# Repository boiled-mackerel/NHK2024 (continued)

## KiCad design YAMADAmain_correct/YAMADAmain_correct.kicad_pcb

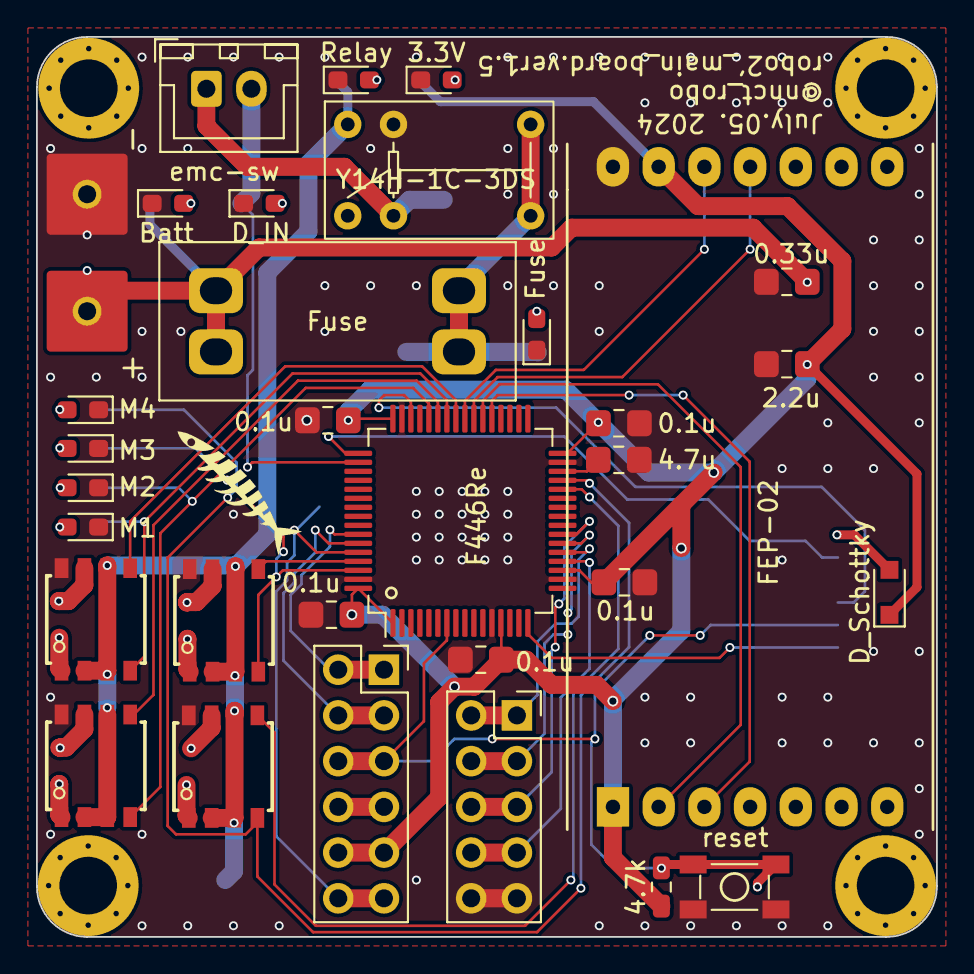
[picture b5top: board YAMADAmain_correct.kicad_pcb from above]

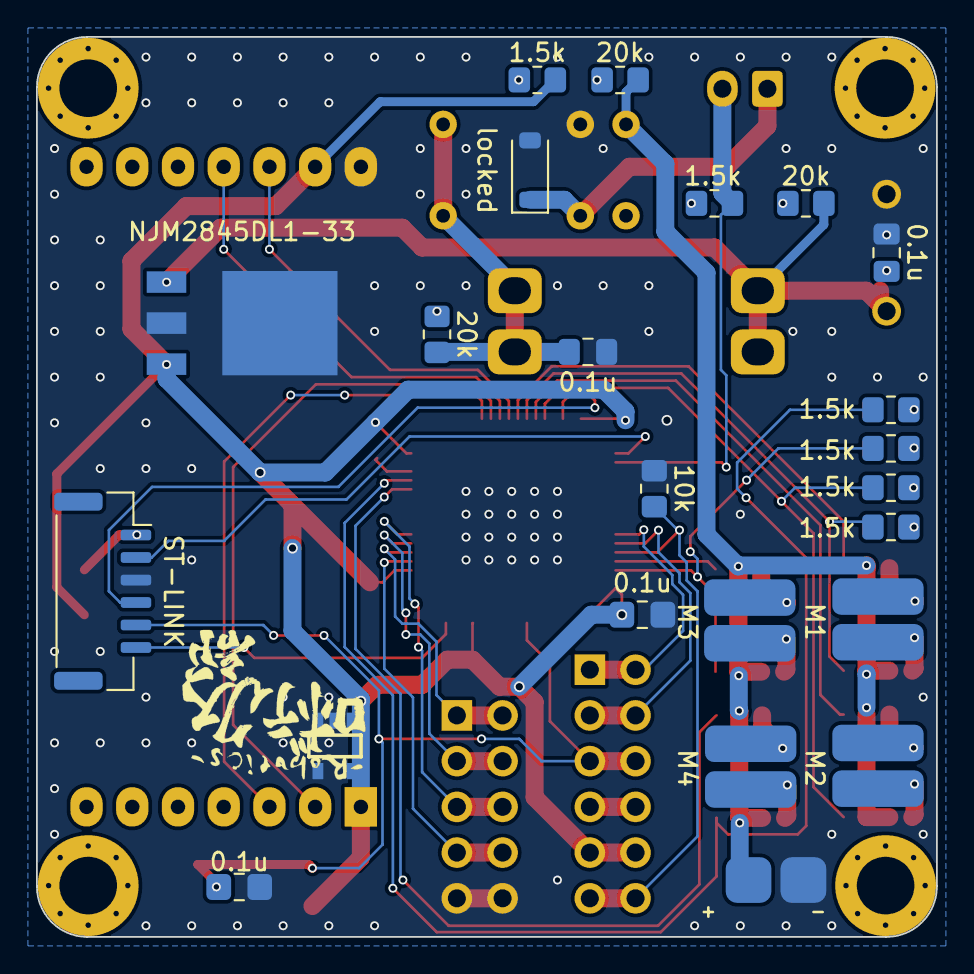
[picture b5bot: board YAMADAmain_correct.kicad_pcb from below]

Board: 2 copper layers, 50.0 x 50.0 mm, 54 parts (22 on the bottom side), 50 nets.

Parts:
B_C1: 0.1u; C_0805_2012Metric_Pad1.18x1.45mm_HandSolder
C1: 0.33u; C_0805_2012
C2: 2.2u; C_0805_2012
D2: 3.3V; LED_0603_1608Metric_Pad1.05x0.95mm_HandSolder
D3: Batt; LED_0603_1608Metric_Pad1.05x0.95mm_HandSolder
D4: Fuse; LED_0603_1608Metric_Pad1.05x0.95mm_HandSolder
D5: D_IN; LED_0603_1608Metric_Pad1.05x0.95mm_HandSolder
D6: locked; D_SOD-123
D7: Relay; LED_0603_1608Metric_Pad1.05x0.95mm_HandSolder
D8: M4; LED_0603_1608Metric_Pad1.05x0.95mm_HandSolder
D9: M3; LED_0603_1608Metric_Pad1.05x0.95mm_HandSolder
D10: M2; LED_0603_1608Metric_Pad1.05x0.95mm_HandSolder
D11: M1; LED_0603_1608Metric_Pad1.05x0.95mm_HandSolder
F1: Fuse; FuseHolder_Carfuse
F_C1: 0.1u; C_0805_2012Metric_Pad1.18x1.45mm_HandSolder
IC1: BD7LS04G-CTL; SOT95P280X125-5N
J1: BATT; POWER_PAD
J2: Conn_02x06_Counter_Clockwise; PinSocket_2x06_P2.54mm_Vertical
J3: emc-sw; JST_XH_B2B-XH-A_1x02_P2.50mm_Vertical
J4: Conn_02x05_Counter_Clockwise; PinSocket_2x05_P2.54mm_Vertical
J5: motor1; min_motor
J6: motor2; min_motor
J7: motor3; min_motor
J8: motor4; min_motor
R1: 10k; R_0805_2012Metric_Pad1.20x1.40mm_HandSolder
R2, R5, R7, R8, R9, R10: 1.5k; R_0805_2012Metric_Pad1.20x1.40mm_HandSolder
R3, R4, R6: 20k; R_0805_2012Metric_Pad1.20x1.40mm_HandSolder
U1: NJM2845DL1-33
U2: FEP-02; FEP-02_PIN_SOCKET
U3: Y14H-1C-3DS
U4, U5, U6, U7: SOP8
U8: 4.7k; R_0603_1608
U9: D_Schottky; smd_diode_SOD-323_HandSoldering_cus10f30
U10: SW_DP3T; tact_sw_smd_skrpabe10
U11, U12, U14, U17, U18, U20, U21: 0.1u; C_0805_2012
U13: ST-LINK; JST_GH_SM06B-GHS-TB_1x06-1MP_P1.25mm_Horizontal
U15: 4.7u; C_0805_2012
U16: STM32F446RETx-stm32; LQFP-64_10x10mm_P0.5mm

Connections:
+3.3V: C2.1, J2.9, J2.10, R2.2, U1.3 (Vout), U2.1 (VCC(2.5v-5.5v)), U2.13 (PowerOn), U8.1, U9.1 (K), U12.1, U14.1, U16.1 (VBAT), U16.13 (VDDA), U16.19 (VDD), U16.32 (VDD), U16.48 (VDD), U16.64 (VDD), U17.1, U18.1, U20.1, U21.1
+5V: J2.7, J2.8
BAT: B_C1.1, C1.1, F1.1, J1.1, R3.2, U1.1 (Vin)
BOOT0: J2.11, J2.12, R1.1, U16.60 (BOOT0)
EMC_IN: J3.2, R5.2, U16.50 (ADC1_EXTI15/ADC2_EXTI15/ADC3_EXTI15/CEC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)
FEP_INI: U2.11 (/INI), U16.39 (PC8/DCMI_D2/SDIO_D0/SYS_TRACED0/TIM3_CH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)
FEP_RST: U2.12 (/RST), U16.40 (PC9/DAC_EXTI9/DCMI_D3/I2C3_SDA/I2S_CKIN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)
Fuse_out: F1.2, F_C1.1, R4.1, U3.3, U3.6
GND: B_C1.2, C1.2, C2.2, D2.1 (K), D3.1 (K), D4.1 (K), D5.1 (K), D6.2 (A), D7.1 (K), D8.1 (K), D9.1 (K), D10.1 (K), D11.1 (K), F_C1.2, J1.2, J4.9, J4.10, R1.2, U1.2 (GND), U2.14 (GND), U3.5, U4.8 (GND), U5.8 (GND), U6.8 (GND), U7.8 (GND), U10.2, U10.4, U11.1, U12.2, U13.3, U14.2, U15.2, U16.12 (VSSA), U16.18 (VSS), U16.31 (VSS), U16.47 (VSS), U16.63 (VSS), U17.2, U18.2, U20.2, U21.2
M1FIN: R10.2, U4.4 (FIN), U16.42 (DAC_EXTI9/DCMI_D0/I2C3_SMBA/I2S2_CK/SAI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)
M1RIN: U4.5 (RIN), U16.41 (I2C3_SCL/RCC_MCO_1/TIM1_CH1/USART1_CK/U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)
M2FIN: R9.2, U5.4 (FIN), U16.44 (ADC1_EXTI11/ADC2_EXTI11/ADC3_EXTI11/CAN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)
M2RIN: U5.5 (RIN), U16.43 (DCMI_D1/TIM1_CH3/USART1_RX/USB_OTG_FS_I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)
M3FIN: R8.2, U6.4 (FIN), U16.62 (CAN1_TX/DAC_EXTI9/DCMI_D7/I2C1_SDA/I2S2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)
M3RIN: U6.5 (RIN), U16.61 (CAN1_RX/DCMI_D6/I2C1_SCL/SDIO_D4/TIM10_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)
M4FIN: R7.2, U7.4 (FIN), U16.29 (I2C2_SCL/I2S2_CK/SAI1_SCK_A/SPI2_SCK/TI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)
M4RIN: U7.5 (RIN), U16.28 (BOOT1/I2S3_SD/QUADSPI_CLK/SAI1_SD_A/SDI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)
MISO: J4.3, J4.4, U16.22 (ADC1_IN6/ADC2_IN6/DCMI_PIXCLK/I2S2_MCK/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)
MOSI: J4.5, J4.6, U16.23 (ADC1_IN7/ADC2_IN7/I2S1_SD/SPI1_MOSI/TIM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)
NSS: J4.7, J4.8, U16.20 (ADC1_IN4/ADC2_IN4/DAC_OUT1/DCMI_HSYNC/I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)
unnamed: D2.2 (A), R2.1
unnamed: D3.2 (A), R3.1
unnamed: D4.2 (A), R4.2
unnamed: D5.2 (A), R5.1
unnamed: D6.1 (K), J3.1, U3.2
unnamed: D7.2 (A), R6.1
unnamed: D8.2 (A), R7.1
unnamed: D9.2 (A), R8.1
unnamed: D10.2 (A), R9.1
unnamed: D11.2 (A), R10.1
unnamed: U9.2 (A), U13.1
unnamed: U15.1, U16.30 (VCAP_1)
PC_6_Serial6TX: U2.3 (TXD(DataIn)), U16.37 (PC6/DCMI_D0/FMPI2C1_SCL/I2S2_MCK/SDIO_D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)
PC_7_Serial6RX: U2.2 (RXD(DateOut)), U16.38 (PC7/DCMI_D1/FMPI2C1_SDA/I2S2_CK/I2S3_MC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)
RESET: J2.5, J2.6, U8.2, U10.1, U10.3, U11.2, U13.5, U16.7 (NRST)
Relay_out: R6.2, U3.4, U4.2 (VCC), U4.3 (VCC), U4.6 (VREF), U5.2 (VCC), U5.3 (VCC), U5.6 (VREF), U6.2 (VCC), U6.3 (VCC), U6.6 (VREF), U7.2 (VCC), U7.3 (VCC), U7.6 (VREF)
SCK: J4.1, J4.2, U16.21 (ADC1_IN5/ADC2_IN5/DAC_OUT2/I2S1_CK/SPI1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)
ST-LINK(TX): U13.6, U16.16 (ADC1_IN2/ADC2_IN2/ADC3_IN2/TIM2_CH3/TIM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)
SWCLK: U13.2, U16.49 (SYS_JTCK-SWCLK/PA14)
SWDIO: U13.4, U16.46 (SYS_JTMS-SWDIO/PA13)
U0RXD: J2.1, J2.2, U16.58 (CAN2_TX/CEC/DCMI_D5/I2C1_SCL/QUADSPI_BK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)
U0TXD: J2.3, J2.4, U16.59 (DCMI_VSYNC/I2C1_SDA/SPDIFRX_IN0/TIM4_CH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)
motor1_A: J5.1, U4.1 (OUT1)
motor1_B: J5.2, U4.7 (OUT2)
motor2_A: J6.1, U5.1 (OUT1)
motor2_B: J6.2, U5.7 (OUT2)
motor3_A: J7.1, U6.1 (OUT1)
motor3_B: J7.2, U6.7 (OUT2)
motor4_A: J8.1, U7.1 (OUT1)
motor4_B: J8.2, U7.7 (OUT2)

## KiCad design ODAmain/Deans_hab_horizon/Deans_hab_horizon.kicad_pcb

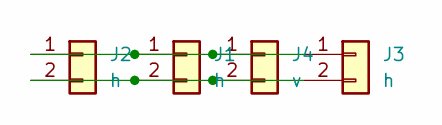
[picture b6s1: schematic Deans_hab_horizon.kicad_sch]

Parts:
J1, J2, J3: h; deans_horizontal
J4: v; Deans_Female

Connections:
unnamed: J1.1, J2.1, J3.1, J4.1
unnamed: J1.2, J2.2, J3.2, J4.2

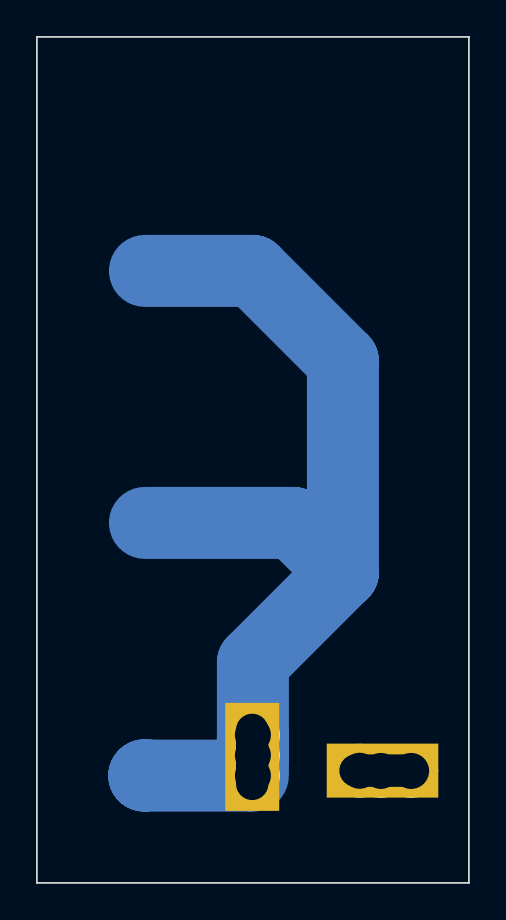
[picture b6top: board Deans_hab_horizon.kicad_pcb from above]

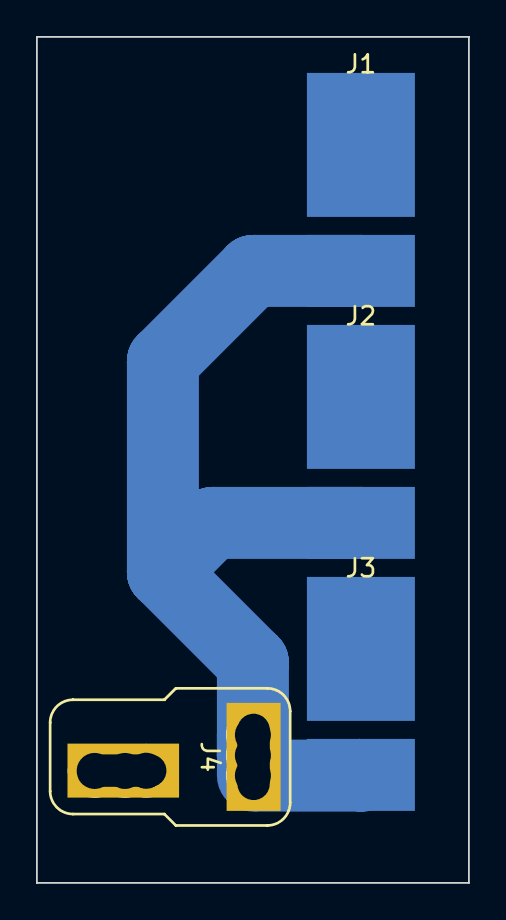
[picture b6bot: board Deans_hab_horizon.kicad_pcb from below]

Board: 2 copper layers, 24.0 x 47.0 mm, 4 parts (4 on the bottom side), 2 nets.

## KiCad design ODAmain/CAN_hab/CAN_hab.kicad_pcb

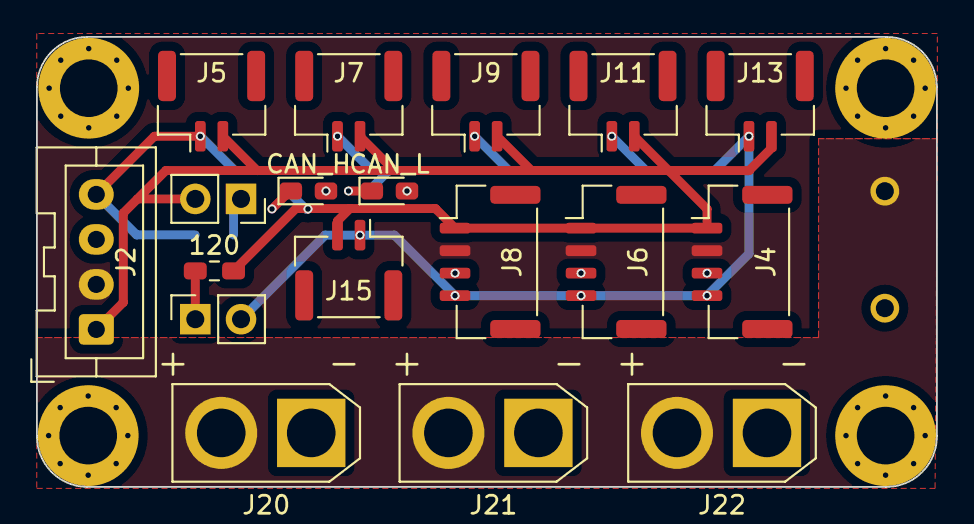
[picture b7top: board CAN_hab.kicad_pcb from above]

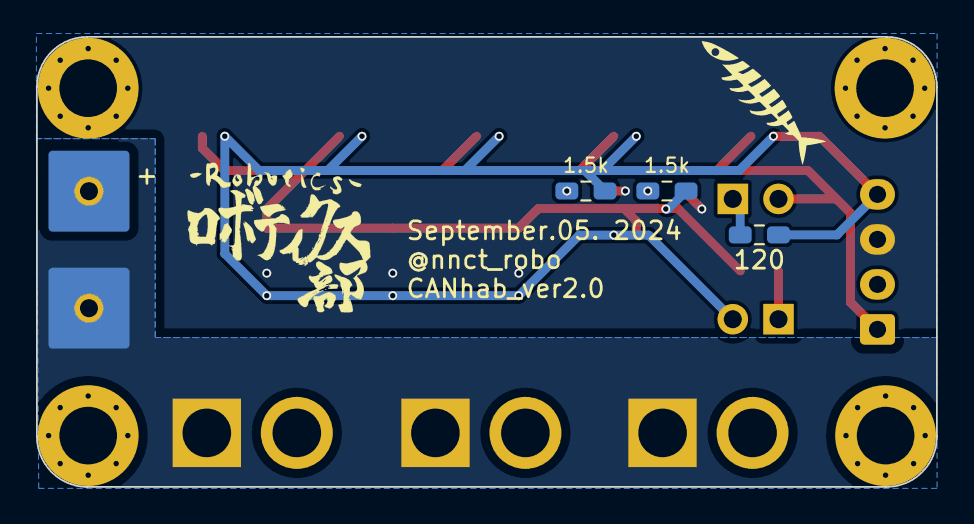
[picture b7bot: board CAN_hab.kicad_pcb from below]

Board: 2 copper layers, 50.0 x 25.0 mm, 22 parts (4 on the bottom side), 10 nets.

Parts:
+: XT30; POWER_PAD_normal
D1: CAN_H; LED_0603_1608
D2: CAN_L; LED_0603_1608
J1, J19: Terminate; PinSocket_1x02_P2.54mm_Vertical
J2: xh; JST_XA_B04B-XASK-1_1x04_P2.50mm_Vertical
J4: gh*4_1; JST_GH_BM04B-GHS-TBT_1x04-1MP_P1.25mm_Vertical
J5: gh*2_1; JST_GH_BM02B-GHS-TBT_1x02-1MP_P1.25mm_Vertical
J6: gh*4_2; JST_GH_BM04B-GHS-TBT_1x04-1MP_P1.25mm_Vertical
J7: gh*2_2; JST_GH_BM02B-GHS-TBT_1x02-1MP_P1.25mm_Vertical
J8: gh*4_3; JST_GH_BM04B-GHS-TBT_1x04-1MP_P1.25mm_Vertical
J9: gh*2_3; JST_GH_BM02B-GHS-TBT_1x02-1MP_P1.25mm_Vertical
J11: gh*2_4; JST_GH_BM02B-GHS-TBT_1x02-1MP_P1.25mm_Vertical
J13: gh*2_5; JST_GH_BM02B-GHS-TBT_1x02-1MP_P1.25mm_Vertical
J15: gh*2_6; JST_GH_BM02B-GHS-TBT_1x02-1MP_P1.25mm_Vertical
J20, J21, J22: XT30; AMASS_XT30U-F_1x02_P5.0mm_Vertical
R1, R4: 120; R_0603_1608
R2, R3: 1.5k; R_0603_1608

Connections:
+5V: J2.2, J4.2, J6.2, J8.2
+BATT: +.2, J20.2, J21.2, J22.2
CAN_H: J2.1, J4.1, J5.2, J6.1, J7.2, J8.1, J9.2, J11.2, J13.2, J15.2, J19.2, R1.1, R2.1
CAN_L: J1.2, J2.4, J4.4, J5.1, J6.4, J7.1, J8.4, J9.1, J11.1, J13.1, J15.1, R3.1, R4.1
GND: D1.1 (K), D2.1 (K), J2.3, J4.3, J6.3, J8.3
GNDPWR: +.1, J20.1, J21.1, J22.1
unnamed: D1.2 (A), R2.2
unnamed: D2.2 (A), R3.2
unnamed: J1.1, R1.2
unnamed: J19.1, R4.2

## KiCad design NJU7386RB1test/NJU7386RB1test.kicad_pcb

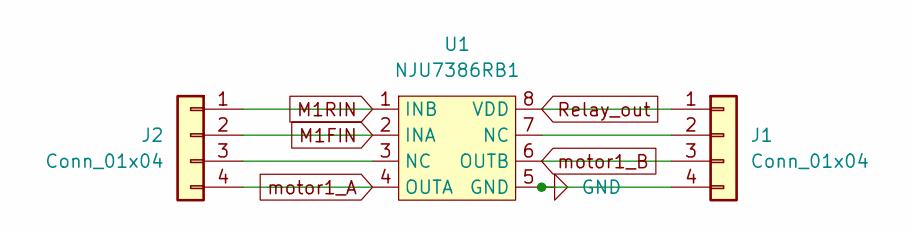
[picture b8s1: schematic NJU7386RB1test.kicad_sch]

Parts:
J1, J2: Conn_01x04; PinSocket_1x04_P2.54mm_Vertical
U1: NJU7386RB1; NJU7386

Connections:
GND: J1.4, U1.5 (GND)
M1FIN: J2.2, U1.2 (INA)
M1RIN: J2.1, U1.1 (INB)
unnamed: J1.2, U1.7 (NC)
unnamed: J2.3, U1.3 (NC)
Relay_out: J1.1, U1.8 (VDD)
motor1_A: J2.4, U1.4 (OUTA)
motor1_B: J1.3, U1.6 (OUTB)

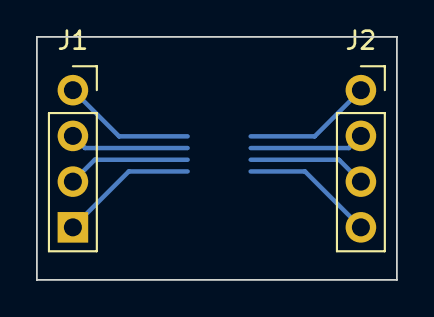
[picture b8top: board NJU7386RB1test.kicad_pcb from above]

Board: 2 copper layers, 20.0 x 13.5 mm, 3 parts (1 on the bottom side), 8 nets.

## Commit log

2024-07-11 init
2024-08-23 2024/08/23
2024-09-22 2024/09/22
2025-03-27 2025/03/27
